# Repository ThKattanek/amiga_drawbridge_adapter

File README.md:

# Amiga DrawBridge Adapter
Here is an adapter for the amiga drawbridge project. Thanks Rob Smith (https://github.com/RobSmithDev/ArduinoFloppyDiskReader) This Adapter include the Atmega328P microcontroller. The adapter can programming over ISP or USB Serial. The bootloader must first flashing on the Atmega328p over the ISP interface.
Here is a video from me in german language -> https://www.youtube.com/watch?v=z-aGWGxyL74

## The circuit board has not yet been tested!

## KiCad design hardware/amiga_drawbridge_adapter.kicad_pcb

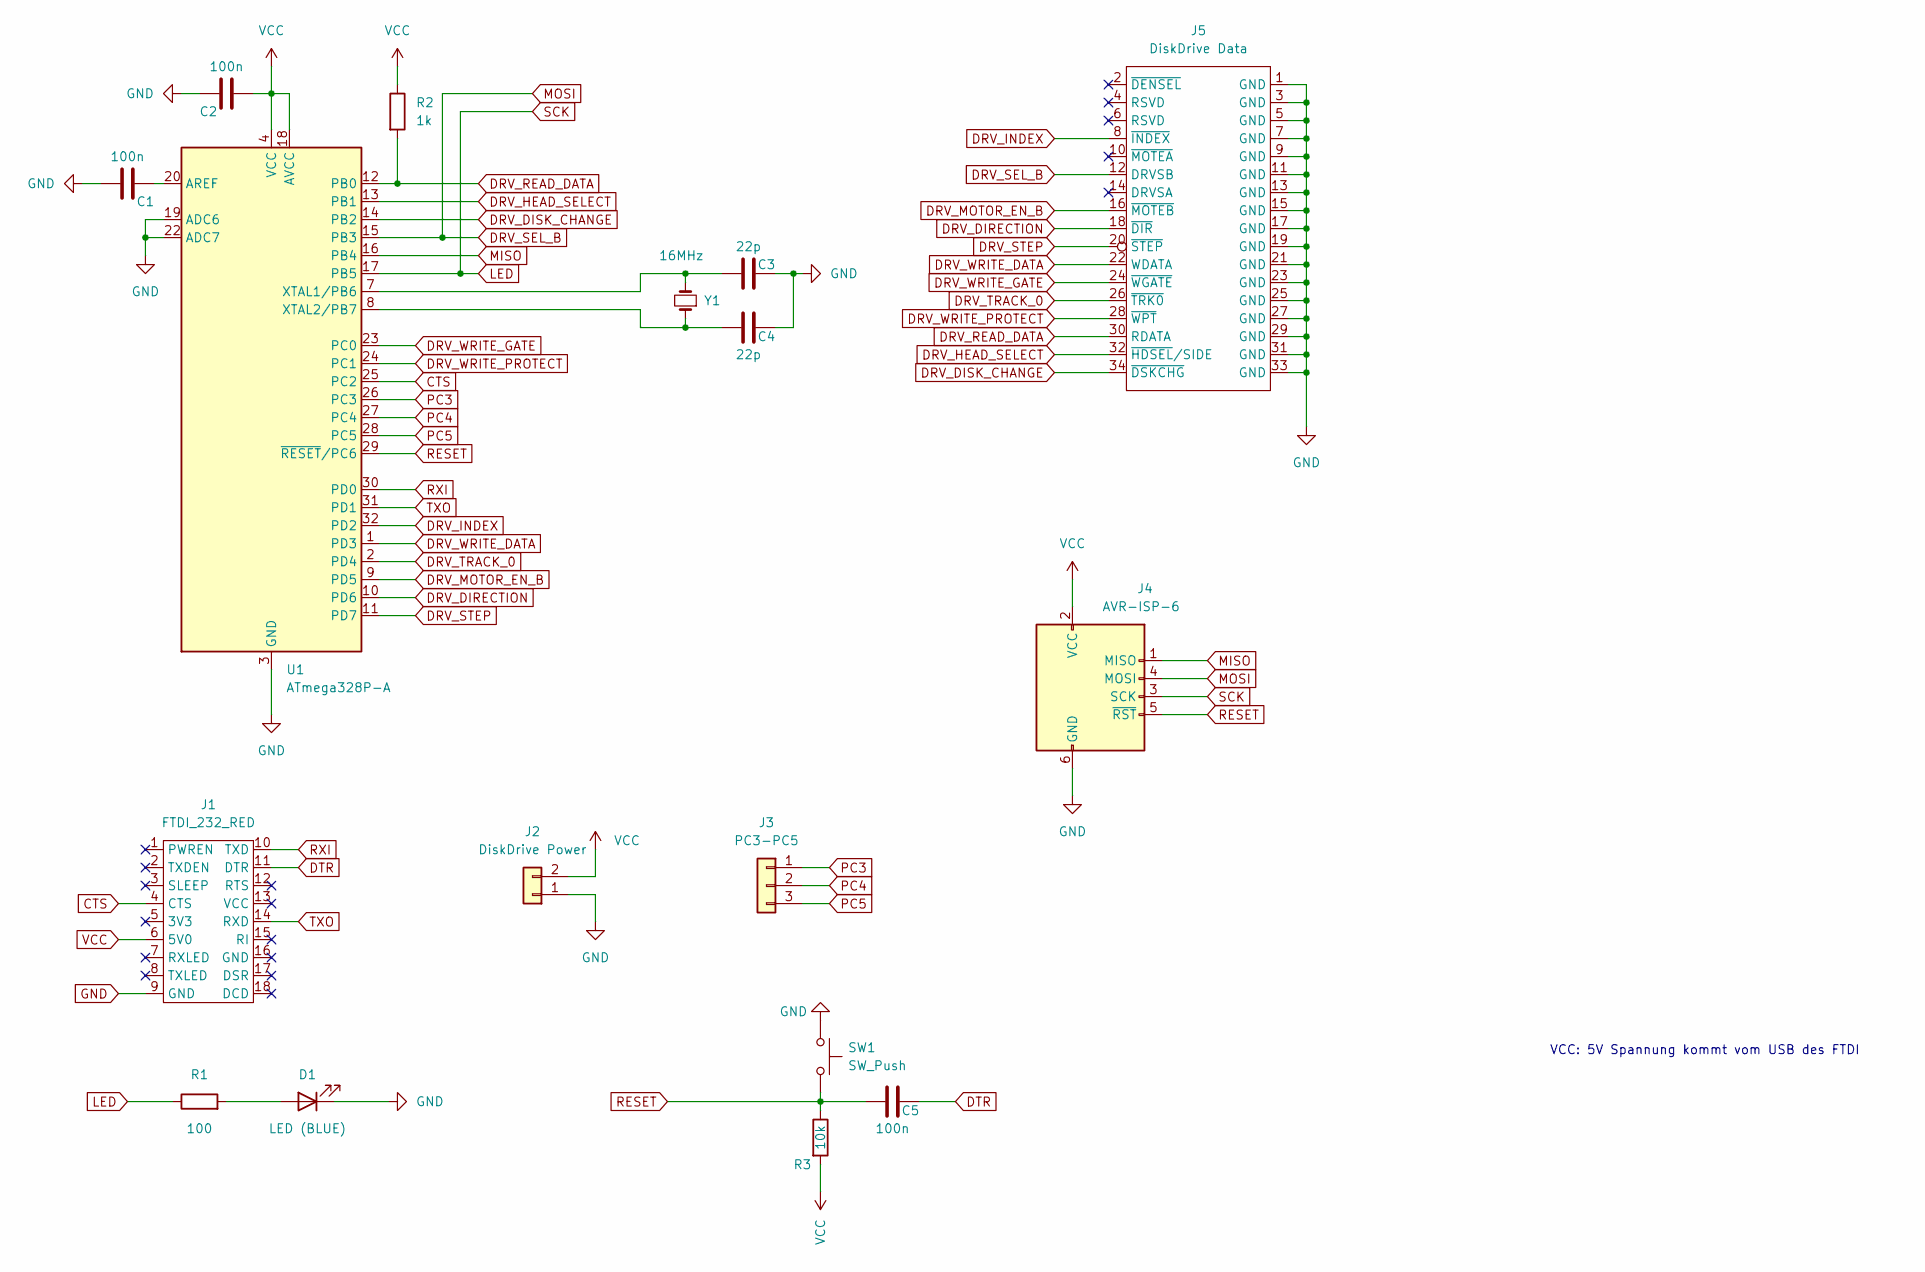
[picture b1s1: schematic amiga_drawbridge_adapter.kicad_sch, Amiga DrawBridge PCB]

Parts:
C1, C2, C5: 100n; C_0805_2012Metric_Pad1.18x1.45mm_HandSolder
C3, C4: 22p; C_0805_2012Metric_Pad1.18x1.45mm_HandSolder
D1: LED (BLUE); LED_D3.0mm
J1: FTDI_232_RED; ftdi_232_red
J2: DiskDrive Power; Molex_KK-254_AE-6410-02A_1x02_P2.54mm_Vertical
J3: PC3-PC5; PinHeader_1x03_P2.54mm_Vertical
J4: AVR-ISP-6; IDC-Header_2x03_P2.54mm_Vertical
J5: DiskDrive Data; PinHeader_2x17_P2.54mm_Vertical
R1: 100; R_0805_2012Metric_Pad1.20x1.40mm_HandSolder
R2: 1k; R_0805_2012Metric_Pad1.20x1.40mm_HandSolder
R3: 10k; R_0805_2012Metric_Pad1.20x1.40mm_HandSolder
SW1: SW_Push; SW_KMR231G
U1: ATmega328P-A; TQFP-32_7x7mm_P0.8mm
Y1: 16MHz; Crystal_SMD_HC49-SD_HandSoldering

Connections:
CTS: J1.4 (CTS), U1.25 (PC2)
DRV_DIRECTION: J5.18 (~DIR), U1.10 (PD6)
DRV_DISK_CHANGE: J5.34 (~DSKCHG), U1.14 (PB2)
DRV_HEAD_SELECT: J5.32 (~HDSEL/SIDE), U1.13 (PB1)
DRV_INDEX: J5.8 (~INDEX), U1.32 (PD2)
DRV_MOTOR_EN_B: J5.16 (~MOTEB), U1.9 (PD5)
DRV_READ_DATA: J5.30 (RDATA), R2.2, U1.12 (PB0)
DRV_SEL_B: J4.4 (MOSI), J5.12 (DRVSB), U1.15 (PB3)
DRV_STEP: J5.20 (~STEP), U1.11 (PD7)
DRV_TRACK_0: J5.26 (~TRK0), U1.2 (PD4)
DRV_WRITE_DATA: J5.22 (WDATA), U1.1 (PD3)
DRV_WRITE_GATE: J5.24 (~WGATE), U1.23 (PC0)
DRV_WRITE_PROTECT: J5.28 (~WPT), U1.24 (PC1)
DTR: C5.2, J1.11 (DTR)
GND: C1.1, C2.2, C3.2, C4.2, D1.1 (K), J1.9 (GND), J2.1, J4.6 (GND), J5.1 (GND), J5.3 (GND), J5.5 (GND), J5.7 (GND), J5.9 (GND), J5.11 (GND), J5.13 (GND), J5.15 (GND), J5.17 (GND), J5.19 (GND), J5.21 (GND), J5.23 (GND), J5.25 (GND), J5.27 (GND), J5.29 (GND), J5.31 (GND), J5.33 (GND), SW1.1, U1.3 (GND), U1.5 (GND), U1.19 (ADC6), U1.21 (GND), U1.22 (ADC7)
LED: J4.3 (SCK), R1.1, U1.17 (PB5)
MISO: J4.1 (MISO), U1.16 (PB4)
unnamed: C1.2, U1.20 (AREF)
unnamed: C3.1, U1.7 (XTAL1/PB6), Y1.2
unnamed: C4.1, U1.8 (XTAL2/PB7), Y1.1
unnamed: D1.2 (A), R1.2
PC3: J3.1, U1.26 (PC3)
PC4: J3.2, U1.27 (PC4)
PC5: J3.3, U1.28 (PC5)
RESET: C5.1, J4.5 (~RST), R3.1, SW1.2, U1.29 (~RESET/PC6)
RXI: J1.10 (TXD), U1.30 (PD0)
TXO: J1.14 (RXD), U1.31 (PD1)
VCC: C2.1, J1.6 (5V0), J2.2, J4.2 (VCC), R2.1, R3.2, U1.4 (VCC), U1.6 (VCC), U1.18 (AVCC)

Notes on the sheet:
VCC: 5V Spannung kommt vom USB des FTDI

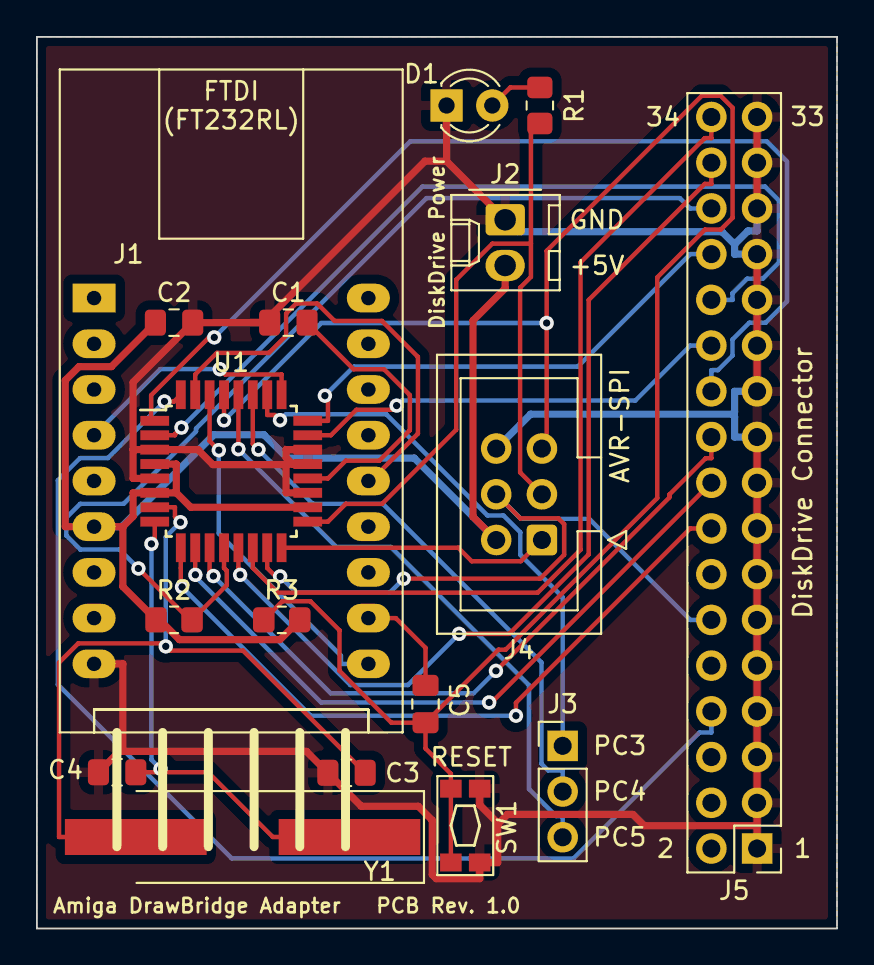
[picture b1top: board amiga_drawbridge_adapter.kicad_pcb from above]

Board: 2 copper layers, 44.4 x 49.5 mm, 17 parts (0 on the bottom side), 28 nets.

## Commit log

2023-04-08 Init commit
2023-04-08 added pictures and routing pcb
2023-05-20 added bom for pcb rev 1.0 as ods file
2023-05-20 added bom to doc
2023-05-20 changed bom
